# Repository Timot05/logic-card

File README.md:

# A kit to learn about logic gates

*written in `ato`*

The enclosure contains a programmable microcontroller, two buttons and an LED. Cards can be plugged on top of the enclosure. They turn on the device and program the buttons to act in the same way described by the card placed on the enclosure.

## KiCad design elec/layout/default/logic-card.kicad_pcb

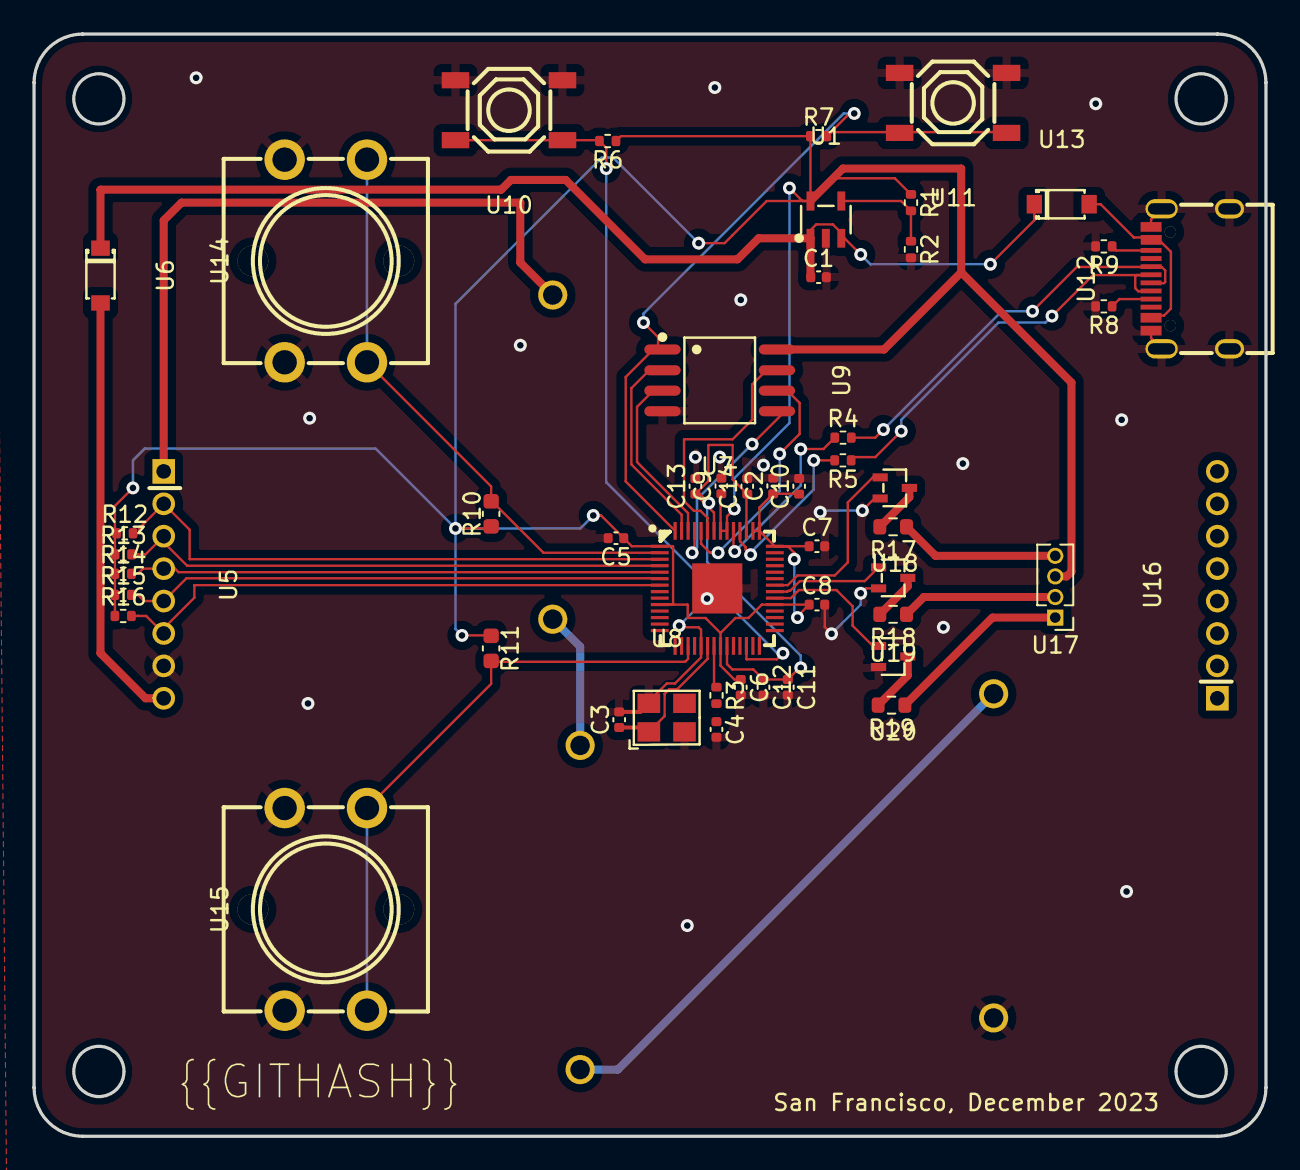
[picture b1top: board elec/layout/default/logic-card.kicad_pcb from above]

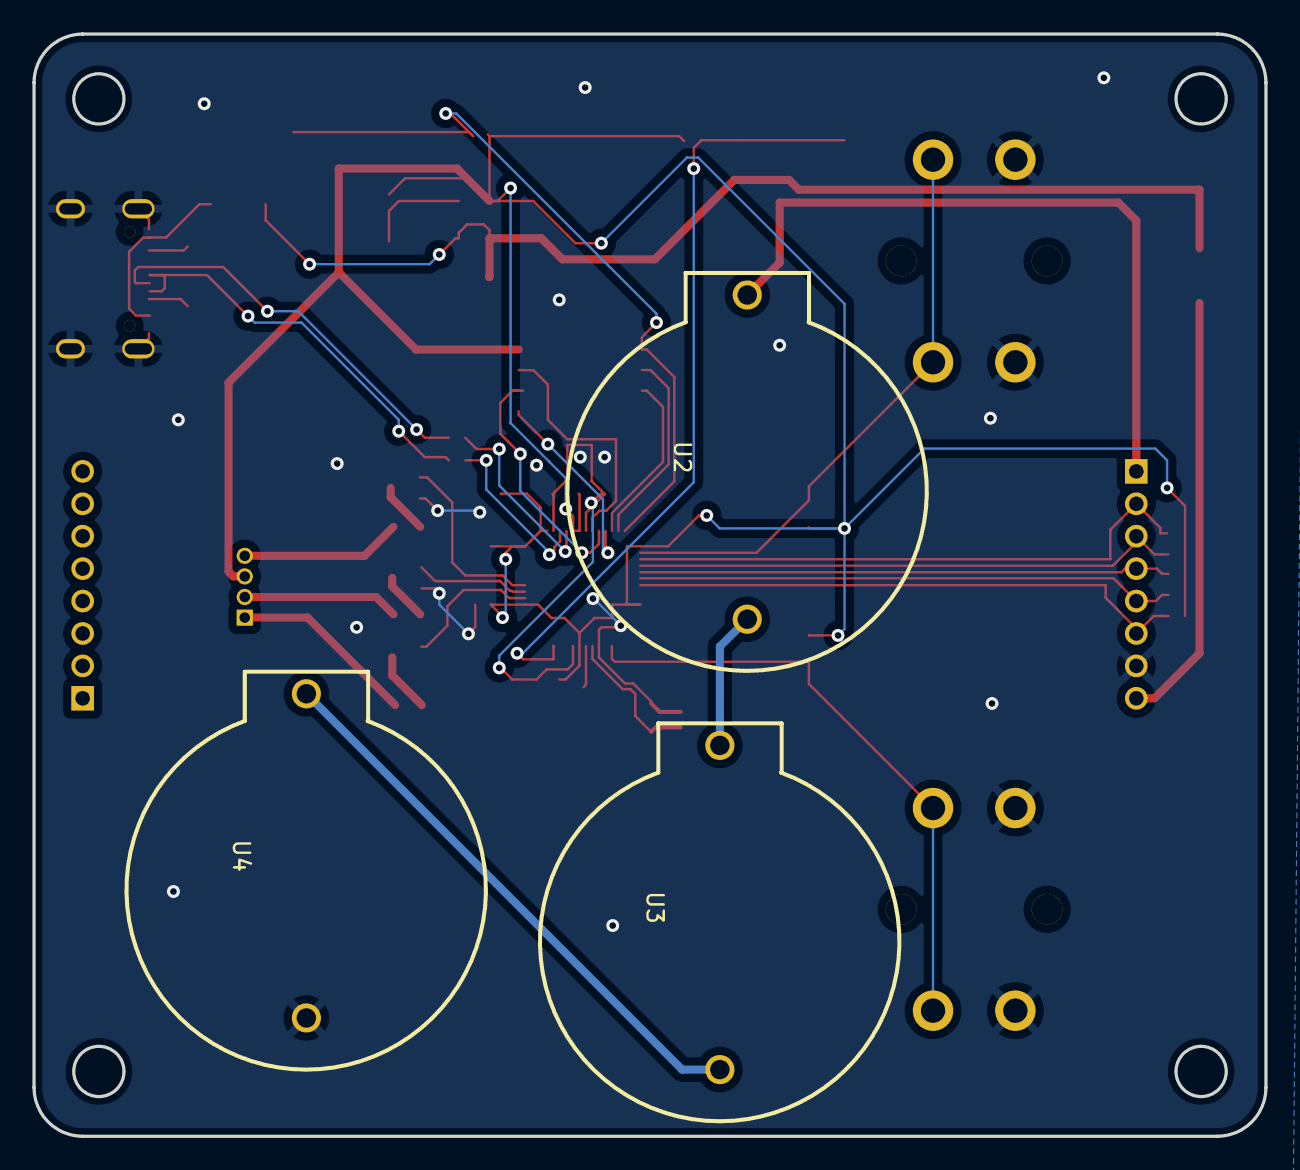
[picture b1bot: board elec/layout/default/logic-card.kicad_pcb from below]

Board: 2 copper layers, 76.0 x 68.0 mm, 53 parts (3 on the bottom side), 42 nets.

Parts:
C1, C2, C10, C14: Multilayer Ceramic Capacitors MLCC - SMD/SMT 1uF 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; C0402
C3, C4: Multilayer Ceramic Capacitors MLCC - SMD/SMT 20pF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; C0402
C5, C6, C7, C8, C9, C11, C12, C13: Multilayer Ceramic Capacitors MLCC - SMD/SMT 100n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; C0402
R1: Chip Resistor - Surface Mount 18KOhms ±5% 1/16W 0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; R0402
R2, R6, R7, R12, R13, R14, R15, R16: 10.0 KΩ; R0402
R3: 1.0 KΩ; R0402
R4, R5: Chip Resistor - Surface Mount 27KOhms ±5% 1/16W 0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; R0402
R8, R9: Chip Resistor - Surface Mount 4.7KOhms ±5% 1/16W 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; R0402
R10, R11: 10.0 KΩ; C0603
R17: 1.5 KΩ; R0603
R18, R19: 100.0 Ω; R0603
U1: SOT-23-5_L3.0-W1.7-P0.95-LS2.8-BL
U2, U3, U4: BAT-TH_BS-02-A1AJ010
U5, U16: HDR-TH_8P-P2.00-V-M
U6, U13: SOD-123_L2.8-W1.8-LS3.7-RD
U7: LQFN-56_L7.0-W7.0-P0.4-EP
U8: OSC-SMD_4P-L3.2-W2.5-BL
U9: SOIC-8_L5.3-W5.3-P1.27-LS8.0-BL
U10, U11: SW-SMD_4P-L5.1-W5.1-P3.70-LS6.5-TL-2
U12: USB-C-SMD_KH-TYPE-C-16P
U14, U15: SW-TH_4P-L12.0-W12.0-P5.00-LS12.5-EH
U17: PinHeader_1x04_P1.27mm_Vertical
U18, U19, U20: SOT-323-3_L2.0-W1.3-P1.30-LS2.1-BR

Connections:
CC1: R8.1, U12.A5
CC2: R9.1, U12.B5
adj: R1.2, R2.1
b_sink: R19.2, U20.3
cs: R7.2, U7.56, U9.1, U11.1, U11.2
dm: R5.1, U12.A7, U12.B7
dp: R4.2, U12.A6, U12.B6
g_sink: R18.2, U19.3
gnd: C1.2, C2.2, C3.2, C4.2, C5.2, C6.2, C7.2, C8.2, C9.2, C10.2, C11.2, C12.2, C13.2, C14.2, R2.2, R8.2, R9.2, U1.2, U4.1, U5.7, U7.19, U7.57, U8.2, U8.4, U9.4, U10.3, U10.4, U11.3, U11.4, U12.1, U12.2, U12.3, U12.4, U12.A1, U12.A12, U12.B1, U12.B12, U14.3, U14.4, U15.3, U15.4, U18.2, U19.2, U20.2
gnd-1: U2.1, U3.2
gnd-2: U3.1, U4.2
gpio0: R10.2, U7.2, U14.1, U14.2
gpio1: R12.2, U5.2, U7.3
gpio2: R13.2, U5.3, U7.4
gpio3: R14.2, U5.4, U7.5
gpio4: R15.2, U5.5, U7.6
gpio5: R16.2, U5.6, U7.7
gpio14: R11.2, U7.17, U15.1, U15.2
gpio22: U7.34, U20.1
gpio23: U7.35, U19.1
gpio24: U7.36, U18.1
io0: U7.53, U9.5
io1: U7.55, U9.2
io2: U7.54, U9.3
io3: U7.51, U9.7
out: U5.8, U6.2
out-1: C4.1, R3.2, U8.3
p1: R17.1, U17.4
p1-1: R18.1, U17.2
p1-2: R19.1, U17.1
r_sink: R17.2, U18.3
run: R6.2, U7.26, U10.1, U10.2
sck: U7.52, U9.6
usb_dm: R5.2, U7.46
usb_dp: R4.1, U7.47
vcc: C1.1, U1.1, U1.3, U6.1, U13.1
vcc-1: C2.1, C5.1, C6.1, C7.1, C8.1, C9.1, C10.1, R1.1, R6.1, R7.1, R10.1, R11.1, R12.1, R13.1, R14.1, R15.1, R16.1, U1.5, U7.1, U7.10, U7.22, U7.33, U7.42, U7.43, U7.44, U7.48, U7.49, U9.8, U17.3
vcc-2: U2.2, U5.1
vcc-3: C11.1, C12.1, C13.1, C14.1, U7.23, U7.45, U7.50
vcc-4: U12.A4, U12.A9, U12.B4, U12.B9, U13.2
xin: C3.1, U7.20, U8.1
xout: R3.1, U7.21

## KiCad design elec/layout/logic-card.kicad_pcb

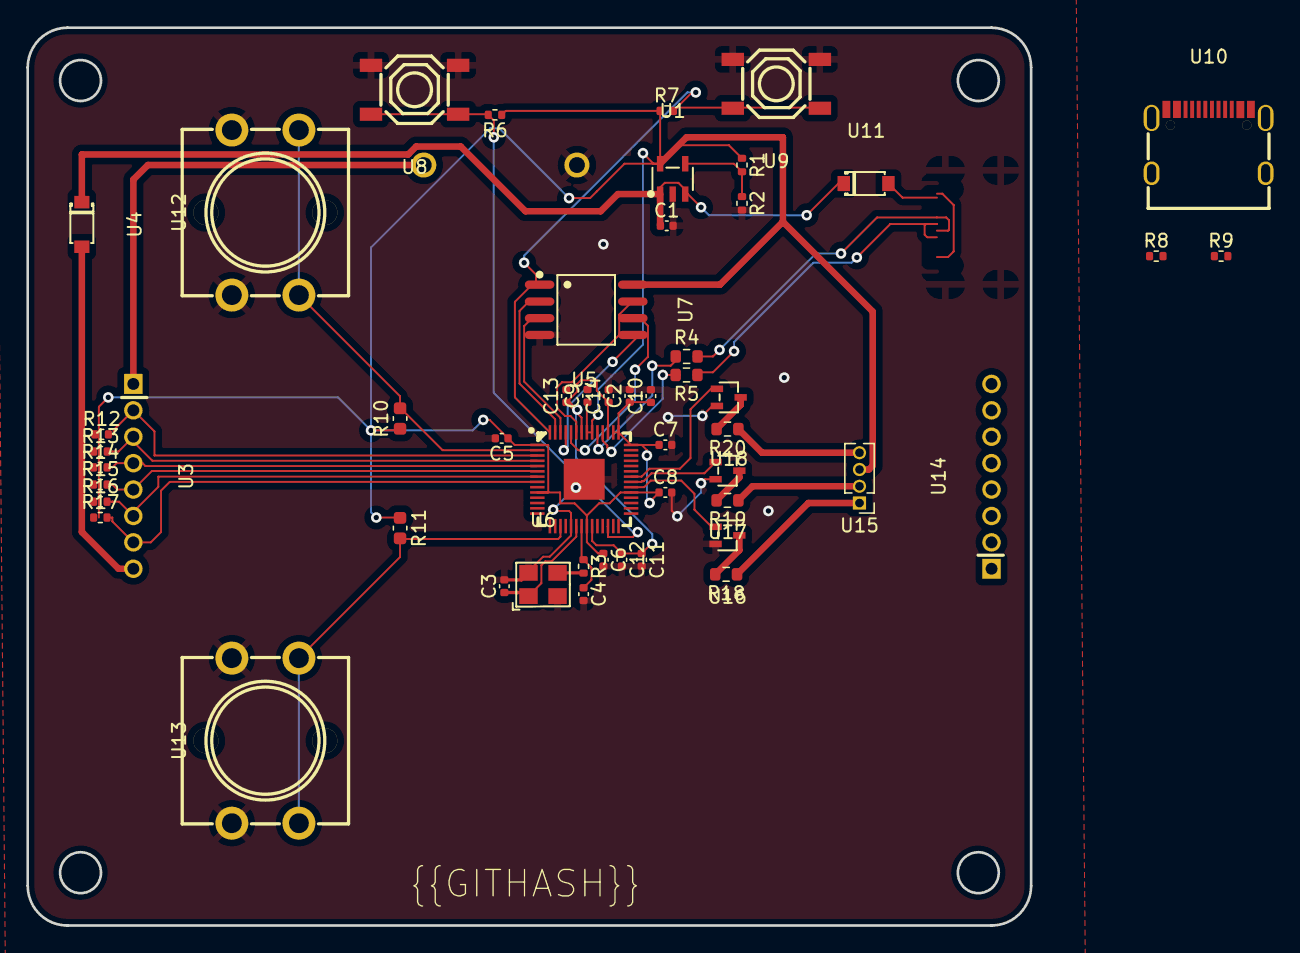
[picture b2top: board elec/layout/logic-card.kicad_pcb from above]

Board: 2 copper layers, 76.0 x 68.0 mm, 52 parts (1 on the bottom side), 41 nets.

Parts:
C1, C2, C10, C14: 1uF; C0402
C3, C4: 20pF; C0402
C5, C6, C7, C8, C9, C11, C12, C13: 100nF; C0402
R1: 18k; R0402
R2, R6, R7, R12, R13, R14, R15, R16, R17: 10k; R0402
R3: 1k; R0402
R4, R5: 27R; R0603
R8, R9: 5.1k; R0402
R10, R11: 10k; C0603
R18: 1.5K; R0603
R19, R20: 100; R0603
U1: <help! no value>; SOT-23-5_L3.0-W1.7-P0.95-LS2.8-BL
U2: <help! no value>; BAT-TH_BH-AAA-A1AJ024
U3, U14: <help! no value>; HDR-TH_8P-P2.00-V-M
U4, U11: <help! no value>; SOD-123_L2.8-W1.8-LS3.7-RD
U5: <help! no value>; LQFN-56_L7.0-W7.0-P0.4-EP
U6: <help! no value>; OSC-SMD_4P-L3.2-W2.5-BL
U7: <help! no value>; SOIC-8_L5.3-W5.3-P1.27-LS8.0-BL
U8, U9: <help! no value>; SW-SMD_4P-L5.1-W5.1-P3.70-LS6.5-TL-2
U10: <help! no value>; USB-C-SMD_KH-TYPE-C-16P
U12, U13: <help! no value>; SW-TH_4P-L12.0-W12.0-P5.00-LS12.5-EH
U15: <help! no value>; PinHeader_1x04_P1.27mm_Vertical
U16, U17, U18: <help! no value>; SOT-323-3_L2.0-W1.3-P1.30-LS2.1-BR

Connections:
CC1: R8.1, U10.A5
CC2: R9.1, U10.B5
adj: R1.2, R2.1, U1.4
b_sink: R20.2, U18.3
cs: R7.2, U5.56, U7.1, U9.1, U9.2
dm: R5.1, U10.A7, U10.B7
dp: R4.2, U10.A6, U10.B6
g_sink: R19.2, U17.3
gnd: C1.2, C2.2, C3.2, C4.2, C5.2, C6.2, C7.2, C8.2, C9.2, C10.2, C11.2, C12.2, C13.2, C14.2, R2.2, R8.2, R9.2, U1.2, U2.1, U5.19, U5.57, U6.2, U6.4, U7.4, U8.3, U8.4, U9.3, U9.4, U10.1, U10.2, U10.3, U10.4, U10.A1, U10.A12, U10.B1, U10.B12, U12.3, U12.4, U13.3, U13.4, U16.2, U17.2, U18.2
gpio0: R10.2, U5.2, U12.1, U12.2
gpio1: R12.2, U3.2, U5.3
gpio2: R13.2, U3.3, U5.4
gpio3: R14.2, U3.4, U5.5
gpio4: R15.2, U3.5, U5.6
gpio5: R16.2, U3.6, U5.7
gpio6: R17.2, U3.7, U5.8
gpio14: R11.2, U5.17, U13.1, U13.2
gpio22: U5.34, U16.1
gpio23: U5.35, U17.1
gpio24: U5.36, U18.1
io0: U5.53, U7.5
io1: U5.55, U7.2
io2: U5.54, U7.3
io3: U5.51, U7.7
out: U3.8, U4.2
out-1: R3.2, U6.3
p1: C4.1, R3.1, U5.21
p1-1: R18.1, U15.1
p1-2: R19.1, U15.2
p1-3: R20.1, U15.4
plus: U2.2, U3.1
r_sink: R18.2, U16.3
run: R6.2, U5.26, U8.1, U8.2
sck: U5.52, U7.6
usb_dm: R5.2, U5.46
usb_dp: R4.1, U5.47
vcc: C1.1, U1.1, U1.3, U4.1, U11.1
vcc-1: C2.1, C5.1, C6.1, C7.1, C8.1, C9.1, C10.1, R1.1, R6.1, R7.1, R10.1, R11.1, R12.1, R13.1, R14.1, R15.1, R16.1, R17.1, U1.5, U5.1, U5.10, U5.22, U5.33, U5.42, U5.43, U5.44, U5.48, U5.49, U7.8, U15.3
vcc-2: C11.1, C12.1, C13.1, C14.1, U5.23, U5.45, U5.50
vcc-3: U10.A4, U10.A9, U10.B4, U10.B9, U11.2
xin: C3.1, U5.20, U6.1

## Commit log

2023-11-14 add readme
2023-11-14 add gitignore and ci
2023-11-14 add layout, lib, ato code
2023-11-14 add kicad lib and chip in layout
2023-11-14 fix ci
2023-11-14 move kicad layout around
2023-11-14 add metadata file
2023-11-15 added a few more comments, added a cap so we can show connections, modified kicad project lib path as it was broken
2023-11-15 added links to docs
2023-11-15 fix typo
2023-11-15 MIT license
2023-11-15 add mech folder and git hash
2023-11-17 Update CI to use more stable containers
2023-11-18 Add 'modules' as submodule
2023-11-21 add venv to gitignore
2023-11-26 remove components from the lib
2023-11-26 remove defaults
2023-11-26 fix CI job
2023-11-26 debug flag to ci
2023-11-26 simplify readme
2023-11-26 move git submodules to root
2023-11-26 move gitsubmodule
2023-11-26 remove the old layout
2023-11-27 Add support for dev containers
2023-12-05 Initial commit for testing123
2023-12-08 Remove targets from ato.yaml and tidy README
2023-12-08 Rename all the things that became testing123
2023-12-09 Initial commit for logic-card
2023-12-10 progress
2023-12-10 outline
2023-12-10 update the rp2040 kit
2023-12-10 add some buttons
2023-12-10 last footprint
2023-12-11 finished up
2023-12-11 update ci
2023-12-11 stabil junge
2023-12-11 fix ato.yaml
2023-12-11 nits
2023-12-11 remove vis.yaml
2023-12-16 update gitignore
2023-12-16 update the layout
2023-12-16 add a few layouts
2023-12-16 fix ato yaml
2023-12-16 switch to coin cells
2023-12-16 card or
2023-12-16 card and
2023-12-16 add button outlines
2024-01-01 update gitignore with pio
2024-01-01 add firmware
2024-01-01 fix the led pins
2024-01-01 fix oscillator
2024-01-05 fix rp2040 version
2024-01-06 update ci for github
2024-01-06 add image
2024-01-06 update the language spec
2024-01-10 Update CI to use atopile-kicad contiainer
2024-01-10 Use container only to do the build
2024-01-10 Send commands via bash
2024-01-11 bump CI
2024-01-11 Simplify
2024-01-11 Remove args from ci build
2024-01-11 Spec version of generics
2024-01-11 Add other cards
2024-01-11 Use production CI image
2024-01-15 add modes, fix for broken card
2024-01-15 mod build config
2024-01-20 test
2024-01-24 Uprev to v0.3.0
2024-01-26 switch ldo
2024-01-28 change the pin connectors to pogopin
2024-02-01 Rever ato version requirement
2024-02-05 Fix fp-lib-table and UUIDs
2024-02-07 Downgrade to pick existing tags
2024-02-08 fix the build
2024-02-08 add new layout
